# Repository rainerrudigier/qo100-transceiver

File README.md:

# QO100 SDR Transceiver Projekt für narrowband Betrieb

## Info

In diesem Github Repo sind die Infos zum OE9 QO-100 Transceiver Project aus dem Jahr 2021/22. Weiter Infos sind auch im QSP 9/22, 10/22 und 11/22 zu finden.

Die Teile des Projekts welche vom Team selbst erstellt wurden sind Open-Source. Sollten diese Teile des Projekts weiter verwendet werden erfolgt das [as-is und ohne Gewähr](/LICENSE).
Für die Fertig-Komponenten die verwendet wurden gelten die entsprechenden Lizenzen und Terms.

## Ziel des Projekts

Ziel ist der Aufbau eines kompakten und einfachen Transceivers für den narrowband (NB) SSB Betrieb über den Amateurfunksatelliten QO-100. Der Aufbau sollte verständlich sein und anderen OMs ermöglichen einfach zu einem Gerät zu kommen. Das Design sollte getestet und möglichst stabil sein, damit ein einfacher Aufbau und eine einfache Bedienung möglich ist.

## Design Kriterien

- Kompakter Aufbau - Formfaktor eines ICOM 7300 (H/B/T 90 / 240 / 238 mm)
- Zentrale Komponente für den Transceiver ist der Adalm PlutoSDR Rev D (Clock Einspeisung ohne Umbau)
- 2400MHz TX über db4um 1W pre-amp und SG-Labs AMP2400 Version 2 20W PA - Es wurde bewusst die V2 Variante gewählt, da die Version 3 Variante: (a) 40mW (16 dBm) Eingangssignal braucht, was zuviel output für den Pluto ist; und (b) es (scheinbar) Probleme mit der Stabilität gibt
- LNBP sollte kurzschlussfest sein; Schutz des Bias-T bei Kurzschluss 
- Anschluss des Systems über USB zum Laptop
- Verwendung der [SDR-Console](https://www.sdr-radio.com/download) von Simon Brown 
- Nur  narrowband (NB) Betrieb - wideband (WB) würde zu viele Änderungen brauchen (Filter, PA,...); der Aufbau wird dann zu komplex
- System sollte von Standard 13.8V DC betrieben werden können (ein Betrieb bis 24V DC wäre gut) (Anschluss Anderson PowerPole)
- Anzeige der wichtigsten Betriebsparameter über ein 4x20 LCD display (Leistung, SWR,...)
- PTT Steuerung - sowohl Betrieb über Fußschalter mit Rückmeldung an die SDR-Console und Betrieb über die SDR-Console mit Aktivierung remote PTT
- PA Abschaltung bei schlechtem SWR - Blockierung der PTT
- Keine remote Bedienelemente im Gehäuse selbst (SDR-Console unterstützt MIDI basierte remote Steuerung); wenn benötigt als abgesetztes eigenständiges Gerät

## Blockschaltbild

## Adalm Pluto

Der Analog Devices [Adalm PlutoSDR](https://wiki.analog.com/university/tools/pluto) ist die Zentrale Komponente für den SDR Transceiver - er ermöglicht das Empfang und Senden von 325Mhz - 3.8GHz; mit 200kHz - 20MHz Bandbreite. Damit wird ermöglicht dass 739-740MHz downlink QO-100 IF Signal vom LNB zu empfangen und das 2400MHz uplink Signal direkt zu erzeugen

Hardware Details können unter [Analog Wiki](https://wiki.analog.com/university/tools/pluto/hacking/hardware) gefunden werden

### Firmware

Update firmware auf letzten Stand (May 2021 -> V0.33) sollte gemacht werden. Details können auf im [Analog Wiki](https://wiki.analog.com/university/tools/nopluto/users/firmware) gefunden werden.

Der Update wird über das emulierte USB Drive des Plutos gemacht.

[Firmware Sourcecode](https://github.com/analogdevicesinc/plutosdr-fw) und [HDL Code](https://github.com/analogdevicesinc/hdl/tree/hdl_2016_r2/projects/pluto) kann auf github gefunden werden 

Eine Firmware Variante die im DATV Bereich verwendet ist bekommt man von F5OEO - dies hat auch noch ein paar extra Features wie PTT über die GPIO pins am Pluto - für den NB SSB Betrieb ist diese PTT Variante aber zu langsam - [github F5OEO](https://github.com/F5OEO/plutosdr-fw)

### Treiber

Treiber für den Adalm PlutoSDR können auch vom [Analog Wiki](https://wiki.analog.com/university/tools/pluto/drivers/windows) heruntergeladen werden

Die Treiber werden für die COM und RNDIS Schnittstellen gebraucht - da der Pluto Ethernet over USB macht.

Wenn die Treiber installiert sind kann man per Putty (oder anderem SSH client) auf den Pluto zugreifen

Zugriff auf die Konsole wird gebraucht um die verschiedenen Parameter (e.g. externe Clock) einzustellen.

Die SDR Console verwendet auch die RNDIS Ethernet Schnittstelle für die Verbindung.

## Externer Clock

### Pluto Rev D

Mit der Rev D des PlutoSDR kann dieser ohne Umbau direkt mit einem externen Clock signal versorgt werden; bei den älteren Revisionen musst durch Umbau entweder ein stabilerer (+/- 0.2 ppm) TCXO oder ein externer GPSDO Anschluss eingebaut werden (auslöten des TCXO am Pluto und Einbau einer SMA Buchse).

Das Einspeisen eines externen Clocks ist nötig um die benötigte Frequenzstabilität zu erreichen; um NB SSB Betrieb fahren zu können, da mit Sprachkanälen im kHZ bandbreiten Bereich gearbeitet wird; und ein ständiges nachjustieren der Frequenz extrem mühsam ist. 

Der primäre Fokus beim Clock des PlutoSDR ist die TX Frequenz Mischer stabilisierung - der downlink Mischer im LNB wird über modifizieren des LNB (Einbau TCXO) oder die PSK Bake stabilisiert.

Für unseren Einsatz wird die Einspeisung eines 40MHZ clocks angewendet welcher von einem Leo Bodnar GPSDO erzeugt wird; wie im Blockschaltbild dargestellt

Zum Anschluss muss ein u.FL auf SMA pigtail verwendet werden das am CLK_IN Eingang angeschlossen wird und am GPSDO - uU muss ein Dämpfungsglied zwischen GPSDO und Pluto verwendet werden damit die **max +10dBm** Eingangsleistung (an 50Ohm) nicht überschritten werden.

Die Aktivierung des CLK_IN erfolgt über einen GPIO Pin des FPGAs und wird über eine Umgebungsvariable im Linux des Plutos aktiviert

Unter https://wiki.analog.com/university/tools/pluto/devs/booting ist die entsprechende Information zu finden bzgl den Umgebungsvariablen für den clock

Umgebungsvariablen werden zB so gesetzt (siehe https://wiki.analog.com/university/tools/pluto/users/customizing) 

Die Standardwerte beim Pluto sind die Nutzung des internen clocks; und die Werkskalibierung des TXCO

Folgendes muss ausgeführt werden um den refclk auf die externe 40MHz source zu stellen

```
fw_setenv refclk_source external
fw_printenv refclk_source
#
fw_setenv ad936x_ext_refclk_override "<40000000>"
fw_printenv ad936x_ext_refclk_override
#
fw_setenv ad936x_skip_ext_refclk 1
fw_printenv ad936x_skip_ext_refclk
#
pluto_reboot reset
#
```

Werte können mit folgendem Kommando überprüft werden

```
# fw_printenv | grep refclk | grep -v setenv
```

### Umbau Rev B Pluto

*TODO infos einfuegen*

## Transceiver System Clock Erzeugung

Für den Betrieb mit QO-100 müssen die System Frequenzen stabilisiert werden. Grundsätzlich gibt es zwei Bereiche für welche ein stabiler Clock wichtig ist:

1. **PlutoSDR 40MHz Clock** - hier ist der Fokus nicht primär auf der absoluten Frequenz selbst - jedoch muss diese “langzeit” stabil sein i.e. kein driften und möglichst kleines Phasenrauschen. Ein driften und/oder wobbeln der Frequenz führt dazu das die Ausgangs Frequenz schwankt - da die 40MHz System Frequenz auf 2400MHz hoch gemischt werden; der standardmäßig verbaute TCXO ist im Bereich von  ±25ppm - was nicht ausreicht um einen stabilen Betrieb zu machen.
2. **LNB downconvert auf IF** - im LNB wird durch einen Mischer das 9.75GHz Eingangssignal auf 740MHz (für QO-100) herunter gemischt - dafür wird je nach LNB ein 25MHz oder 27MHz Quarz verwendet (DRO Varianten können nicht verwendet werden) welche die 9.75GHz Mischer Frequenz erzeugt - im regulären TV SAT betrieb wird der Träger vom Satelliten Software technisch gelocked - dadurch ist ein Frequenzdrift durch Temperatur oder andere Einflüsse nicht weiter tragisch. Diese Methode kann auch für QO-100 (PSK baken synchronisation) angewendet werden, ist jedoch nicht immer zuverlässig; es kann aber auch das LNB umgebaut werden und entsprechen per TCXO oder GPSDO mit einem stabilen CLK versorgt werden.

Für die Versorgung des Systems mit einem stabilen Clock wurde die GPSDO Variante gewählt. Der PlutoSDR und das LNB werden mit einem GPSDO von Leo Bodnar versorgt.

## GPSDO Clock Leo Bodnar

Der [zwei Kanal GSPDO von Leo Bodnar](http://www.leobodnar.com/shop/index.php?main_page=product_info&cPath=107&products_id=234) ist ein GPS disziplinierter TCXO auf der Basis eines UBLOX GPS Modules und einer Clock PLL (Si5328C) mit TCXO.

Der UBLOX kann einen stabilen Puls mit der Frequenz von 1Hz bis 10MHz liefern. Der SI5328C kann dann durch die entsprechende Parameter die Ausgänge beschalten. Der TCXO am SI5328C wird als basis verwendet und entsprechend dem GPS puls gezogen. Dadurch entsteht eine sehr genau, stabile und low-jitter Ausgangs Frequenz.

*TODO blockschaltbild einfügen*

Der GPSDO kann mittels eine einfachen Software konfiguriert werden und entsprechende eingestellt werden das er 40MHz und 25MHz liefert. Die entsprechende Parameter müssen selbst eingegeben werden - da die SW selbst nur bestimmt Frequnz kombination Standardmäßig zulässt.

Beim startup des GPSDO liefert dieser den entsprechende Clock sofort; fix und lock des systems auf GPS und PLL dauert ca 30 Sek bei Kaltstart des GPS.

### Parameter für 40MHz / 25MHz

OE6MUE hat im [Amsat Forum](https://forum.amsat-dl.org/index.php?thread/2823-gpsdo-dual-channel-from-leo-bodnar-how-to-configure/&postID=8896#post8896) folgende Parameter beschrieben:

```
40mhz+25mhz einstellungen nochmal korrigiert da der jitter nicht gepasst hat, jetzt ok!!)
CKIN1: 1750000
N31: 15
N2_HS: 4
N2_LS: 12000
N1_HS: 7
NC1_LS: 20
NC2_LS: 32
"update" drücken, soft schließen und erneut öffnen, fertig
vy 73 de oe6mue, mike aus graz
```
Die verschiedenen Parameter erzeugen unterschiedlich F3 (PLL Vergleichs-) Frequenzen; laut dem Datenblatt sollte F3 möglichst hoch sein - damit der Jitter besser ist. (Daher verwende ich die Parameter welche DSPLLsim ermittelt hat 250kHz F3). 

Mit diesen Parameters wird am Output1 40MHz ausgegeben und am Output2 25MHz

### Firmware Upgrade Leo Bodnar GPSDO

**Achtung** .. Firmware Upgrade GPSDO setzt alle Werte Retour! AUCH DIE LEISTUNG AM AUSGANG! Nicht bei angeschlossenem Pluto und LNB upgraden

### Clock Einspeisung Pluto 40MHz

Mit einem Rev.D PlutoSDR kann der Systemclock direkt eingespeist werden (**max +10dBM an 50 Ohm**). Die Konfiguration zur Aktivierung des externen Clocks muss entsprechende gemacht werden.

Mit der Einstellung von 8mA Treiber Strom beim GPSDO ergibt 7.7 dBm an 50 Ohm; uU muss aber ein Dämpfungsglied eingesetzt werden wenn die Leistung des GPSDO zum LNB nicht ausreichend ist.

### Clock Einspeisung LNB 25MHz

Das LNB wird mit 25MHz Clock versorgt. Dafür muss das LNB entsprechend Umgebaut werden (siehe LNB )

Der Treiber Strom muss uU angepasst werden je nach Distanz zum LNB

## TX Pfad

Der TX Pfad besteht primär aus Filterung und Verstärkung; die 20W PA bietet genug Leistung um eine gute Strecke zwischen Transceiver und Antenne zu ermögliche. Das verwendete Kabel zur 2.4GHz Antenne sollte low-loss / 2.4GHz ausgelegt sein. Das Signal wird dann über eine POTY Antenne (am Feed des Spiegels) oder per Helix Antenne Richtung Satellit geschickt.

### Pluto TX RF Ausgang

Ausgang sollte nicht mit voller Leistung betrieben werden. Im oberen Leistungsbereich ist der PlutoSDR nicht linear.

[ADALM Pluto TX output power rev1.pdf (dd1us.de)](http://dd1us.de/Downloads/ADALM%20Pluto%20TX%20output%20power%20rev1.pdf)

>Einstellung an der Ausgangsleistung - sdr-console  'Drive' and 'OP Power' controls

### 2.4GHz SAW Filter

Filter für 2.4 GHz um Nebenaussendungen und/oder Mischprodukte zu filtern. Filterung erfolgt gleich nach dem PlutoSDR um mögliche Produkte nicht in weitere folge zu Verstärken und ggf auszusenden 

### 2.4GHz Vor-Verstärker - db4um 2.5W

[db4um 2.5W PA (SKY66292-11)](https://github.com/db4um/PA_13cm_2W)

### 2.4GHz Power Verstärker - SG-Labs 20W Version 2

Als Power PA wird der [SG-Labs 20W Version 2](https://www.sg-lab.com/AMP2400/amp2400.html) Verstärker verwendet. Es wurde bewusst die Version 2 gewählt; da die Version 3 in Kombination mit dem Pluto sub-optional ist durch die input Power Anforderungen der V3 PA (40mW / 16dBM); der Pluto würde dann mit max power laufen und damit uU nicht-linear

Die Ausgangsleistung kann über die Spannungsversorgung (24 - 28 V DC) geregelt werden.

Umbau bzgl VSWR Messung siehe *TODO infos einfuegen*

Achtung Jumper setting auf Position 1 .. PTT on wenn PTT input auf GND *TODO infos einfuegen*

### POTY Antenne

#### Aufbau Poty

[POTY G0MJW / PA3FYM / M0EYT](http://www.hybridpretender.nl/poty.html) -- [PDF](http://www.hybridpretender.nl/patch.pdf)

[Infos von OE7WPA bzgl Patch fuer QO100](https://oe7wpa.com/index.php/projekte/antennen/patchantennen/patchantenne-fuer-qo-100)

#### Dielektrische (RF) Linse für Poty-Feed

*TODO infos einfuegen*

## RX Pfad

### Bias-T

*TODO infos Messung/Simulation einfuegen*

### LNB Spannungsversorgung

Zum Empfang muss das LNB mit Spannungs versorgt werden. Je nach Spannung (13V oder 18V) wird die polarisation des LNB’s eingestellt. 

Für den narrowband Empfang muss das LNB vertikal polarisiert arbeiten - es muss daher mit 13V versorgt werden.

Die 13V werden aus der 5V System Versorgung mittels eines Step-Up Converters erzeugt 

### LNB

#### Funktionsweise

LNBs haben eine PLL für die Erzeugung der Oszillatorfrequenz von 9750 MHz welche für den Mischer gebraucht wird. Das ergibt zunächst eine ausreichende Stabilität für Schmalband Empfang. Die Referenz der PLL ist ein 25 MHz Quarz. Die Satelliten Ausgabe im X-Band ergibt eine ZF von 739,500 bis 740 MHz. Durch die Ungenauigkeit der 25 MHz Quarze kann die Oszillator- und damit die ZF-Frequenz bis zu einigen hundert KHz abweichen.

Für den NB (narrownband) Betrieb wird die Vertical Polarisation (13V) verwendet; für WB (wideband) Horizontale Polarisation.

Für den SDR Transceiver Aufbau haben wir uns narrowband festgelegt.

Diese Ungenauigkeit kann sich durch (a) ersetzen des Quarzes durch einen TCXO oder (b) die Einspeisung des Clocks über einen GPSDO stabilisieren. Die genaue Offset Frequenz muss dann entsprechend in der SDR-Console eingestellt werden (siehe …)

Für den Aufbau des SDR Transceivers wurde die Einspeisung des Clocks von einem Leo Bodnar GPSDO gewählt

#### Umbau LNB

*TODO infos einfuegen*

## USB Verteilung

Die verschiedenen Komponenten im Transceiver werden über USB angebunden. Aus diesem Grund wurden ein USB 2.0 HUB im Transceiver verbaut welcher die verschieden Komponenten zusammenfasst

[Zero4U UUGear](https://www.digikey.at/product-detail/de/adafruit-industries-llc/3298/1528-2083-ND/6834072)

*TODO info 0R Widerstand*

## Spannungsversorgung
Anforderungen der verschiedenen Verbraucher

```
PlutoSDR 5v / 1A
-- plutosdr ist auf 1A limitiert (schematic Seite 8 LTC4415)
USB Hub 5v / 2A
Leo Bodnar 5v / 250mA (über USB Hub)
db4um_PA 5v / 1A
PTT Steuerung & Arduino 5v / 500mA
LNBP_13V 5v / 800mA
SG-Labs PA 24-28v / 1.5A
```

### System Spannung 5V/28V

Die Variante mit den Meanwell DC/DC Wandlern wurde gewählt damit der Formfaktor des Gehäuses auf ein IC7300/IC9700 erreicht werden kann. Da die der Platzverbrauch bei der Variante mit den Meanwell Wandlern sehr gering ist.

*TODO infos einfuegen*

### LNB 13V Spannungsversorgung

Variante mit [LT1372](https://www.analog.com/en/products/lt1372.html)

*TODO infos einfuegen*

## Display und Controller für System Parameter

Das Display und der Controller basieren auf dem design von DC5ZM [Infos siehe](https://hf5l.pl/en/monitor-for-sg-lab-power-amplifier/) - das ursprüngliche Design war primär für die Messung der SG-Labs Parameter (Power DRV, REF, FWD, Spannung) - wurde aber erweitert um noch zusätzlich System Parameter des SDR Transceivers erfassen zu können. Eine Möglichkeit für das abschalten der PA PTT über einen OC Ausgang wurde auch vorgesehen für ein spätere Version, damit bei zu hohem VSWR die PA ausgeschaltet wird .Um das System erweitern zu können wurde ein I2C Port vorgesehen. Das Display wird zur Anzeige der Parameter verwendet und über einen Rotary Encoder kann der Controller gesteuert werden. Als CPU wird ein Arduino Nano verwendet.

### VSWR Messung SG-Labs 20W PA
Die SG-Labs Endstufe hat lamba/4 microstrip direct coupler am Eingang und Ausgang um die Leistung zu messen welche in die PA gehen (DRV) und was zur Antenne und von der Antenne kommt (FWD/REV).

Die verschiedenen Anschlüsse (FWD, REV, DRV) müssen über durchführungs Filter aus dem Alu Gehäuse der 20W PA herausgeführt werden.

*TODO bild einfuegen*

### GPSDO lock Anzeige
Mittels eine Photo-Transistors (OP505W) wird die LED des Leo Bodnar GPSDO an den Controller “gekoppelt” und im Display der entsprechende GPSDO status angezeigt

*TODO infos einfuegen*

## PTT Aktivierung von der SDR Console zum Transceiver

Ein USB Relais kann verwendet werden um das Transmit Signal von der [SDR Console in ein PTT Signal](https://www.sdr-radio.com/relays) umzuwandeln

Es sind einige USB Relais varianten über ebay beziehbar. Wir haben uns jedoch für den Aufbau einer eigenen Variante entschieden. 

Dies hat einen besseren Formfaktor ermöglicht und die Erweiterung für eine besser PTT Anzeige am Gehäuse.

## Gehäuse
Der Formfaktor des ICOM 7300 mit (B × H × T) 240 mm × 94 mm × 238 mm (ohne vorstehende Teile) wurde im Projekt gewählt, da dieser sehr Kompakt und portable ist.

Das Gehäuse wurde komplett aus Alumium Profil-Komponenten aufgebaut. Die verwenden [Eckprofile](https://www.heavymetal-aluminium.de/shop/aluminium/aluminiumprofile/aluminium-eloxiert-aluminiumprofile/gehaeuseprofil-1-natur-eloxiert/gehaeuseprofil-1-natur-eloxiert/) sind standard im Industrie-Gehäusebau und können auf Mass zugeschnitten werden.

## Empfangs Software (PC / Linux)

### Download und installation

Download der software von [https://www.sdr-radio.com/download](https://www.sdr-radio.com/download)

### Einrichtung

*TODO infos einfuegen*

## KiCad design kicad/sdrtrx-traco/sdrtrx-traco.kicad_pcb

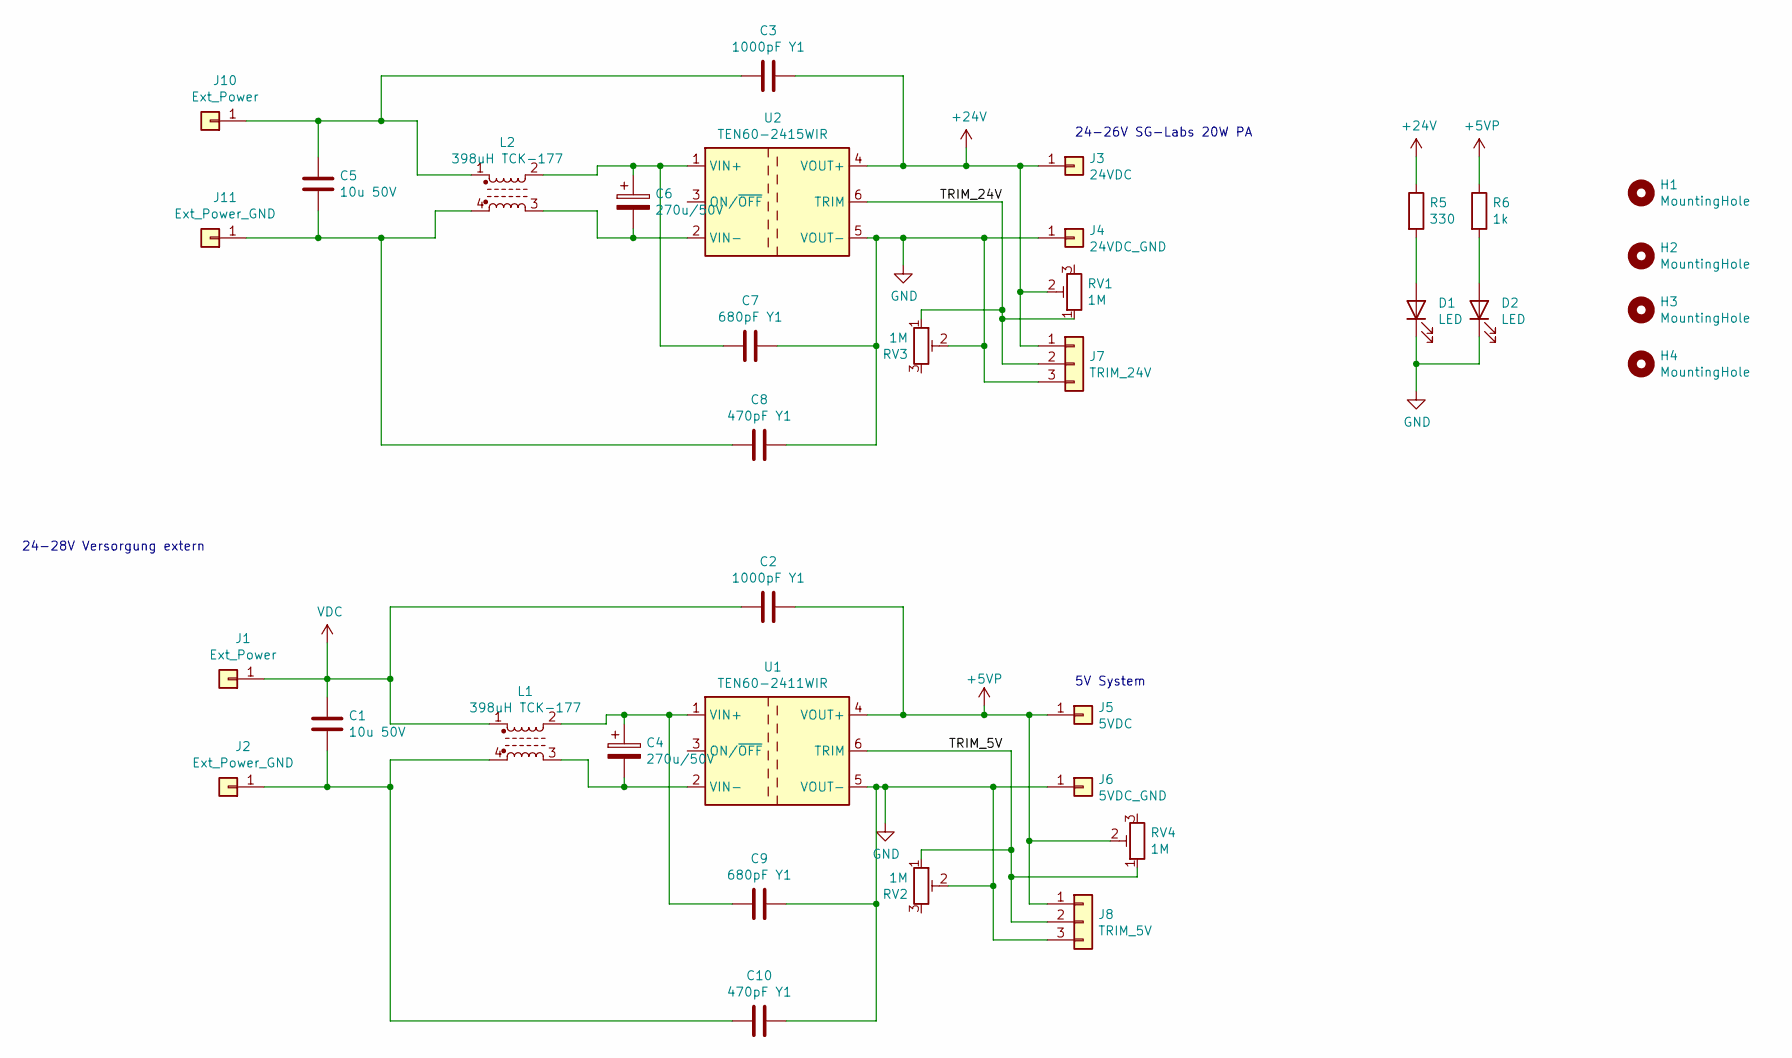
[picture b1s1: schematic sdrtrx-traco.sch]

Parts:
C1, C5: 10u 50V; C_1210_3225Metric_Pad1.42x2.65mm_HandSolder; DigiKey 399-C1210C106K5PAC7210CT-ND
C2, C3: 1000pF Y1; C_Murata_DK1; DigiKey 490-16263-1-ND
C4, C6: 270u/50V; CP_Radial_D10.0mm_P5.00mm
C7, C9: 680pF Y1; C_Murata_DK1; DigiKey 490-16263-1-ND
C8, C10: 470pF Y1; C_Murata_DK1; DigiKey 490-16263-1-ND
D1, D2: LED; LED_0805_2012Metric
H1, H2, H3, H4: MountingHole; MountingHole_3.2mm_M3_Pad
J1, J10: Ext_Power; SolderWire-1sqmm_1x01_D1.4mm_OD2.7mm
J2, J11: Ext_Power_GND; SolderWire-1sqmm_1x01_D1.4mm_OD2.7mm
J3: 24VDC; SolderWire-1sqmm_1x01_D1.4mm_OD2.7mm
J4: 24VDC_GND; SolderWire-1sqmm_1x01_D1.4mm_OD2.7mm
J5: 5VDC; SolderWire-1sqmm_1x01_D1.4mm_OD2.7mm
J6: 5VDC_GND; SolderWire-1sqmm_1x01_D1.4mm_OD2.7mm
J7: TRIM_24V; Molex_PicoBlade_53398-0371_1x03-1MP_P1.25mm_Vertical; DigiKey WM7607CT-ND
J8: TRIM_5V; Molex_PicoBlade_53398-0371_1x03-1MP_P1.25mm_Vertical; DigiKey WM7607CT-ND
L1, L2: 398uH TCK-177; Choke_Traco_TCK-177-16,0x16.0mm
R5: 330; R_0805_2012Metric
R6: 1k; R_0805_2012Metric
RV1, RV2, RV3, RV4: 1M; Potentiometer_Bourns_3269W_Vertical; DigiKey 3269W-1-105GLFCT-ND
U1: TEN60-2411WIR; Converter_DCDC_TRACO_TEN60-xxxx_THT; DigiKey 1951-TEN60-2411WIR-ND
U2: TEN60-2415WIR; Converter_DCDC_TRACO_TEN60-xxxx_THT; DigiKey 1951-TEN60-2415WIR-ND

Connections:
+5VP: C2.2, J5.1, J8.1, R6.1, RV4.2, U1.4 (VOUT+)
+24V: C3.1, J3.1, J7.1, R5.1, RV1.2, U2.4 (VOUT+)
/TRIM_5V: J8.2, RV2.1, RV4.1, U1.6 (TRIM)
/TRIM_24V: J7.2, RV1.1, RV3.1, U2.6 (TRIM)
GND: C7.1, C8.1, C9.1, C10.1, D1.1 (K), D2.1 (K), J4.1, J6.1, J7.3, J8.3, RV2.2, RV3.2, U1.5 (VOUT-), U2.5 (VOUT-)
unnamed: C1.2, C10.2, J2.1, L1.4
unnamed: C3.2, C5.1, J10.1, L2.1
unnamed: C4.1, C9.2, L1.2, U1.1 (VIN+)
unnamed: C4.2, L1.3, U1.2 (VIN-)
unnamed: C5.2, C8.2, J11.1, L2.4
unnamed: C6.1, C7.2, L2.2, U2.1 (VIN+)
unnamed: C6.2, L2.3, U2.2 (VIN-)
unnamed: D1.2 (A), R5.2
unnamed: D2.2 (A), R6.2
VDC: C1.1, C2.1, J1.1, L1.1

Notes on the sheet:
5V System
24-26V SG-Labs 20W PA
24-28V Versorgung extern

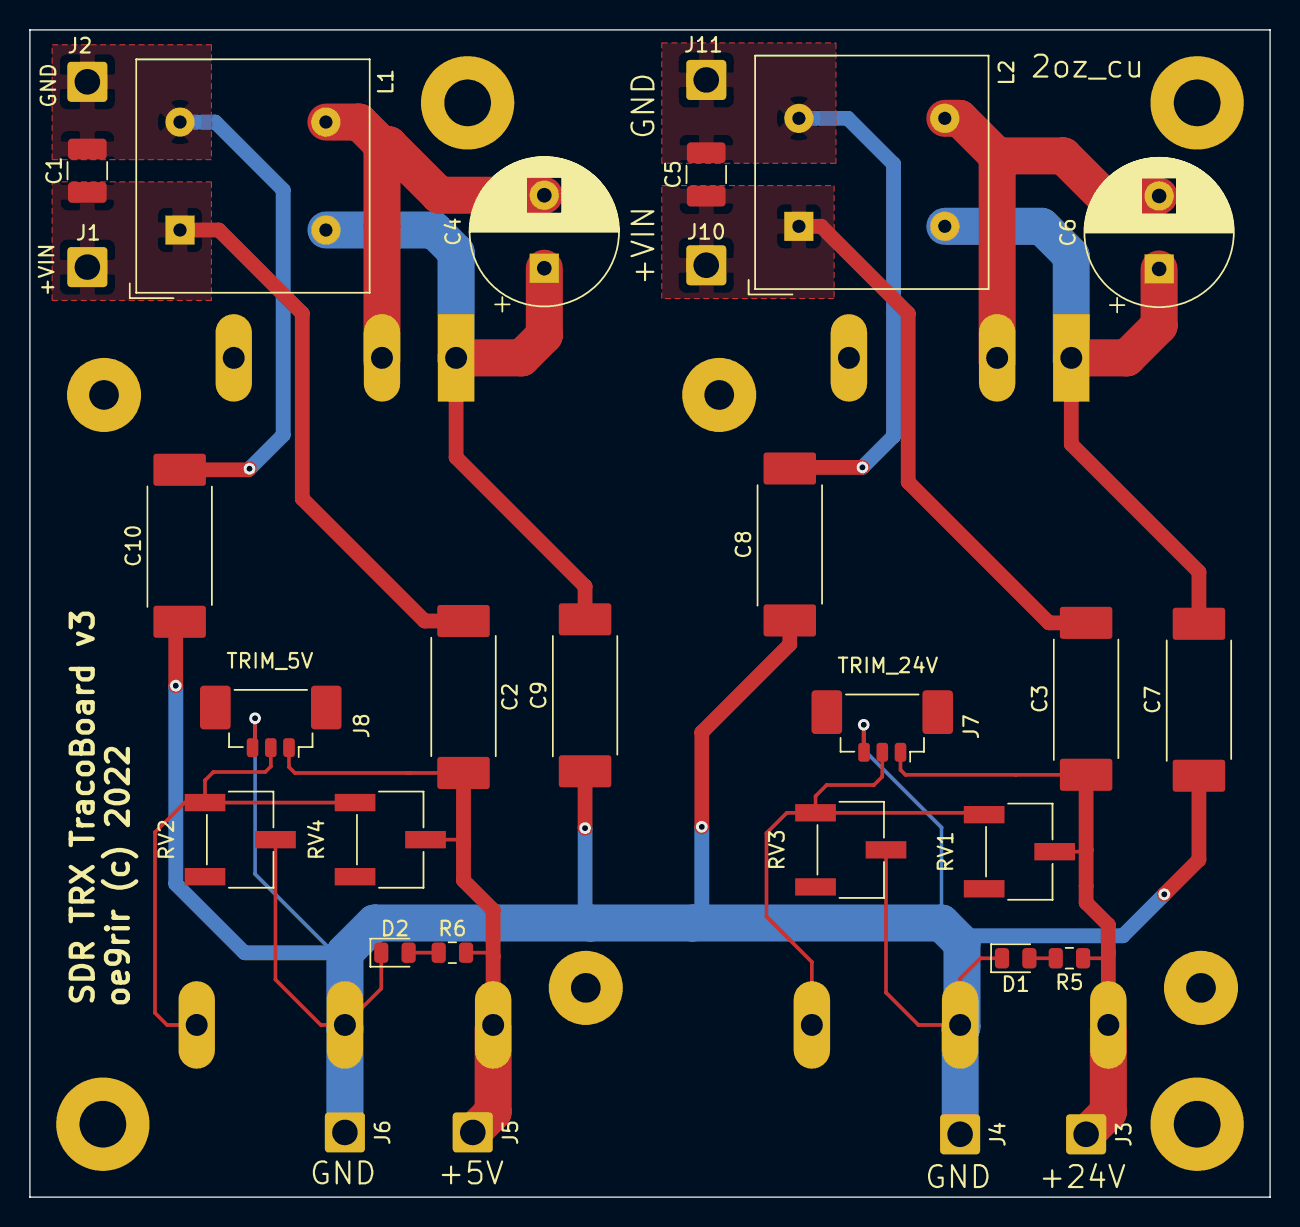
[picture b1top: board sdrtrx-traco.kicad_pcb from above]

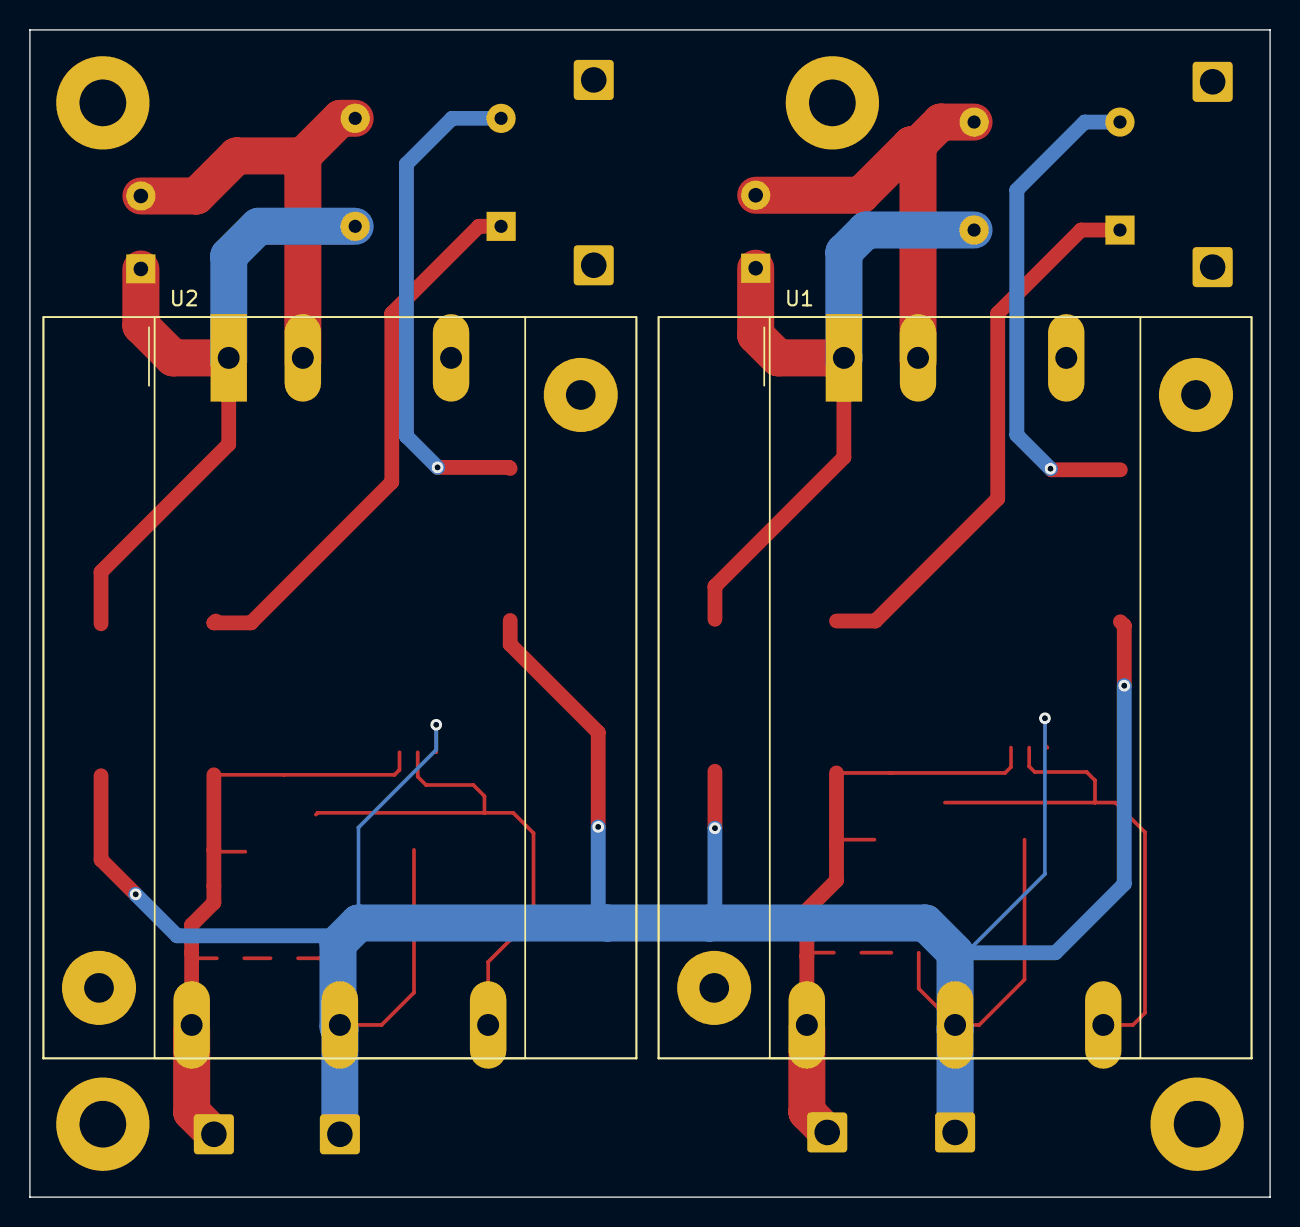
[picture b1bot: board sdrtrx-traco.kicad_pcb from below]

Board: 2 copper layers, 85.0 x 80.0 mm, 36 parts (2 on the bottom side), 15 nets.

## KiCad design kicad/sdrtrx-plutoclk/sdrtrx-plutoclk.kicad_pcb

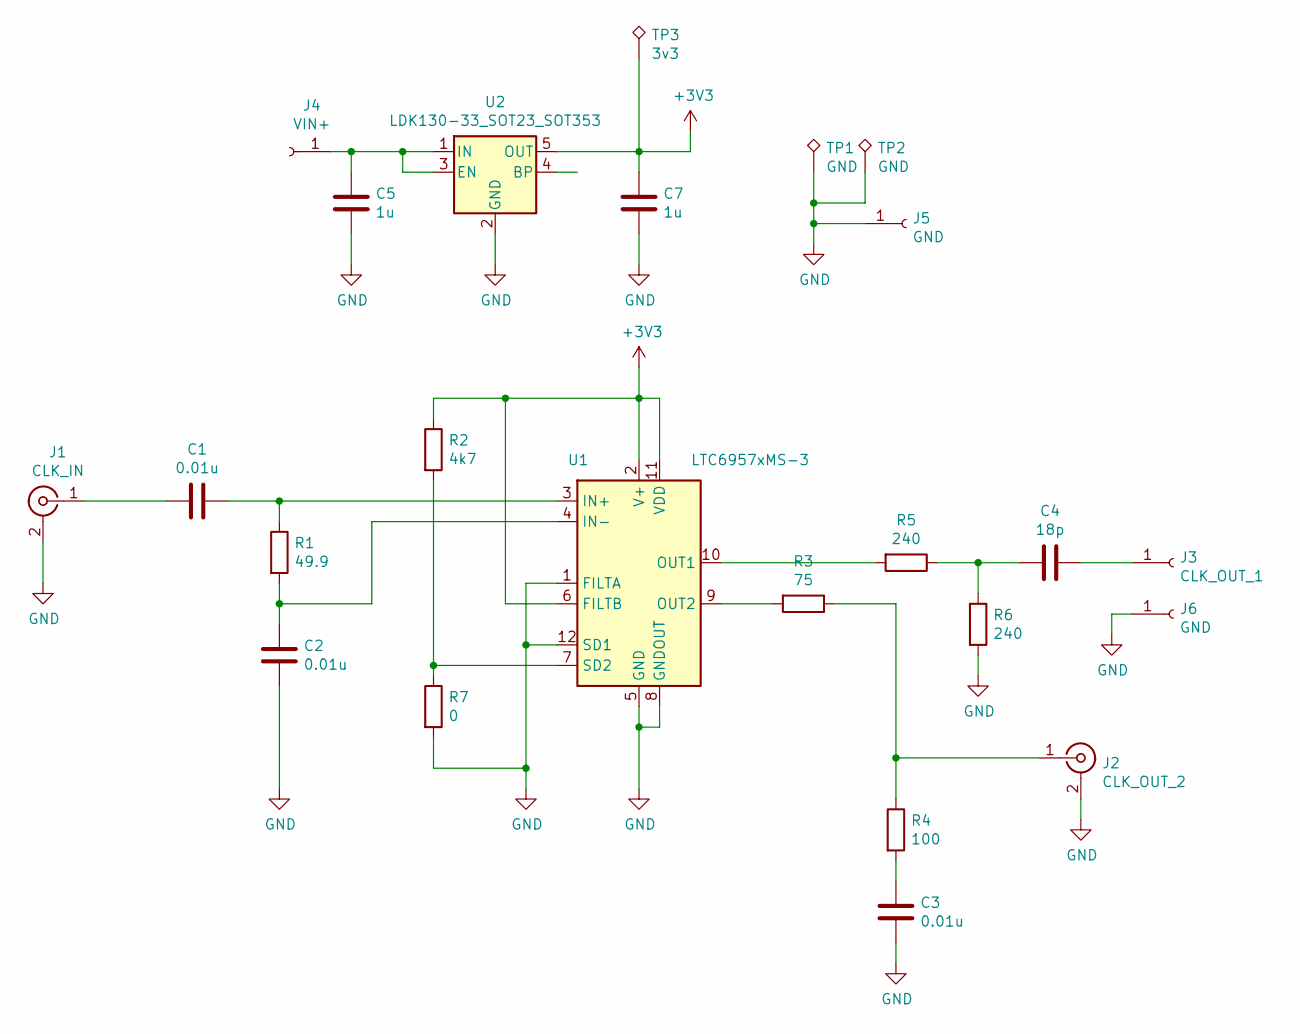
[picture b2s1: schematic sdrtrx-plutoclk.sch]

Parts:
C1, C2, C3: 0.01u; C_0603_1608Metric
C4: 18p; C_0603_1608Metric
C5, C7: 1u; C_0603_1608Metric
J1: CLK_IN; U.FL_Hirose_U.FL-R-SMT-1_Vertical
J2: CLK_OUT_2; U.FL_Hirose_U.FL-R-SMT-1_Vertical
J3: CLK_OUT_1; TestPoint_Pad_1.0x1.0mm
J4: VIN+; TestPoint_Pad_3.0x3.0mm
J5: GND; TestPoint_Pad_3.0x3.0mm
J6: GND; TestPoint_Pad_1.0x1.0mm
R1: 49.9; R_0603_1608Metric
R2: 4k7; R_0603_1608Metric
R3: 75; R_0603_1608Metric
R4: 100; R_0603_1608Metric
R5, R6: 240; R_0603_1608Metric
R7: 0; R_0603_1608Metric
TP1, TP2: GND; TestPoint_Pad_1.0x1.0mm
TP3: 3v3; TestPoint_Pad_1.0x1.0mm
U1: LTC6957xMS-3; MSOP-12_3x4mm_P0.65mm
U2: LDK130-33_SOT23_SOT353; SOT-23-5L; Mouser 511-LDK130M33RY

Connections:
+3V3: C7.1, R2.1, TP3.1, U1.2 (V+), U1.6 (FILTB), U1.11 (VDD), U2.5 (OUT)
GND: C2.2, C3.2, C5.2, C7.2, J1.2 (Ext), J2.2 (Ext), J5.1, J6.1, R6.2, R7.2, TP1.1, TP2.1, U1.1 (FILTA), U1.5 (GND), U1.8 (GNDOUT), U1.12 (SD1), U2.2 (GND)
unnamed: C1.1, R1.1, U1.3 (IN+)
unnamed: C1.2, J1.1 (In)
unnamed: C2.1, R1.2, U1.4 (IN-)
unnamed: C3.1, R4.2
unnamed: C4.1, J3.1
unnamed: C4.2, R5.1, R6.1
unnamed: C5.1, J4.1, U2.1 (IN), U2.3 (EN)
unnamed: J2.1 (In), R3.1, R4.1
unnamed: R2.2, R7.1, U1.7 (SD2)
unnamed: R3.2, U1.9 (OUT2)
unnamed: R5.2, U1.10 (OUT1)

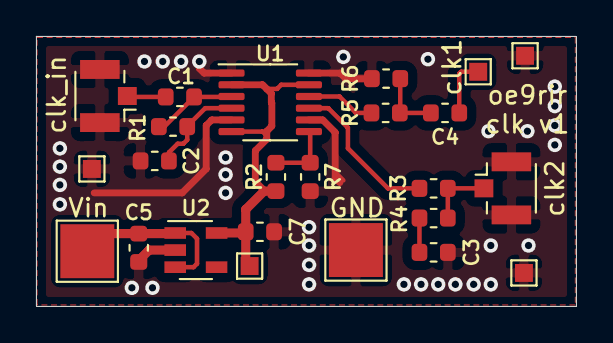
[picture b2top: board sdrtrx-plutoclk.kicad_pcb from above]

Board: 2 copper layers, 30.0 x 15.0 mm, 24 parts (0 on the bottom side), 13 nets.

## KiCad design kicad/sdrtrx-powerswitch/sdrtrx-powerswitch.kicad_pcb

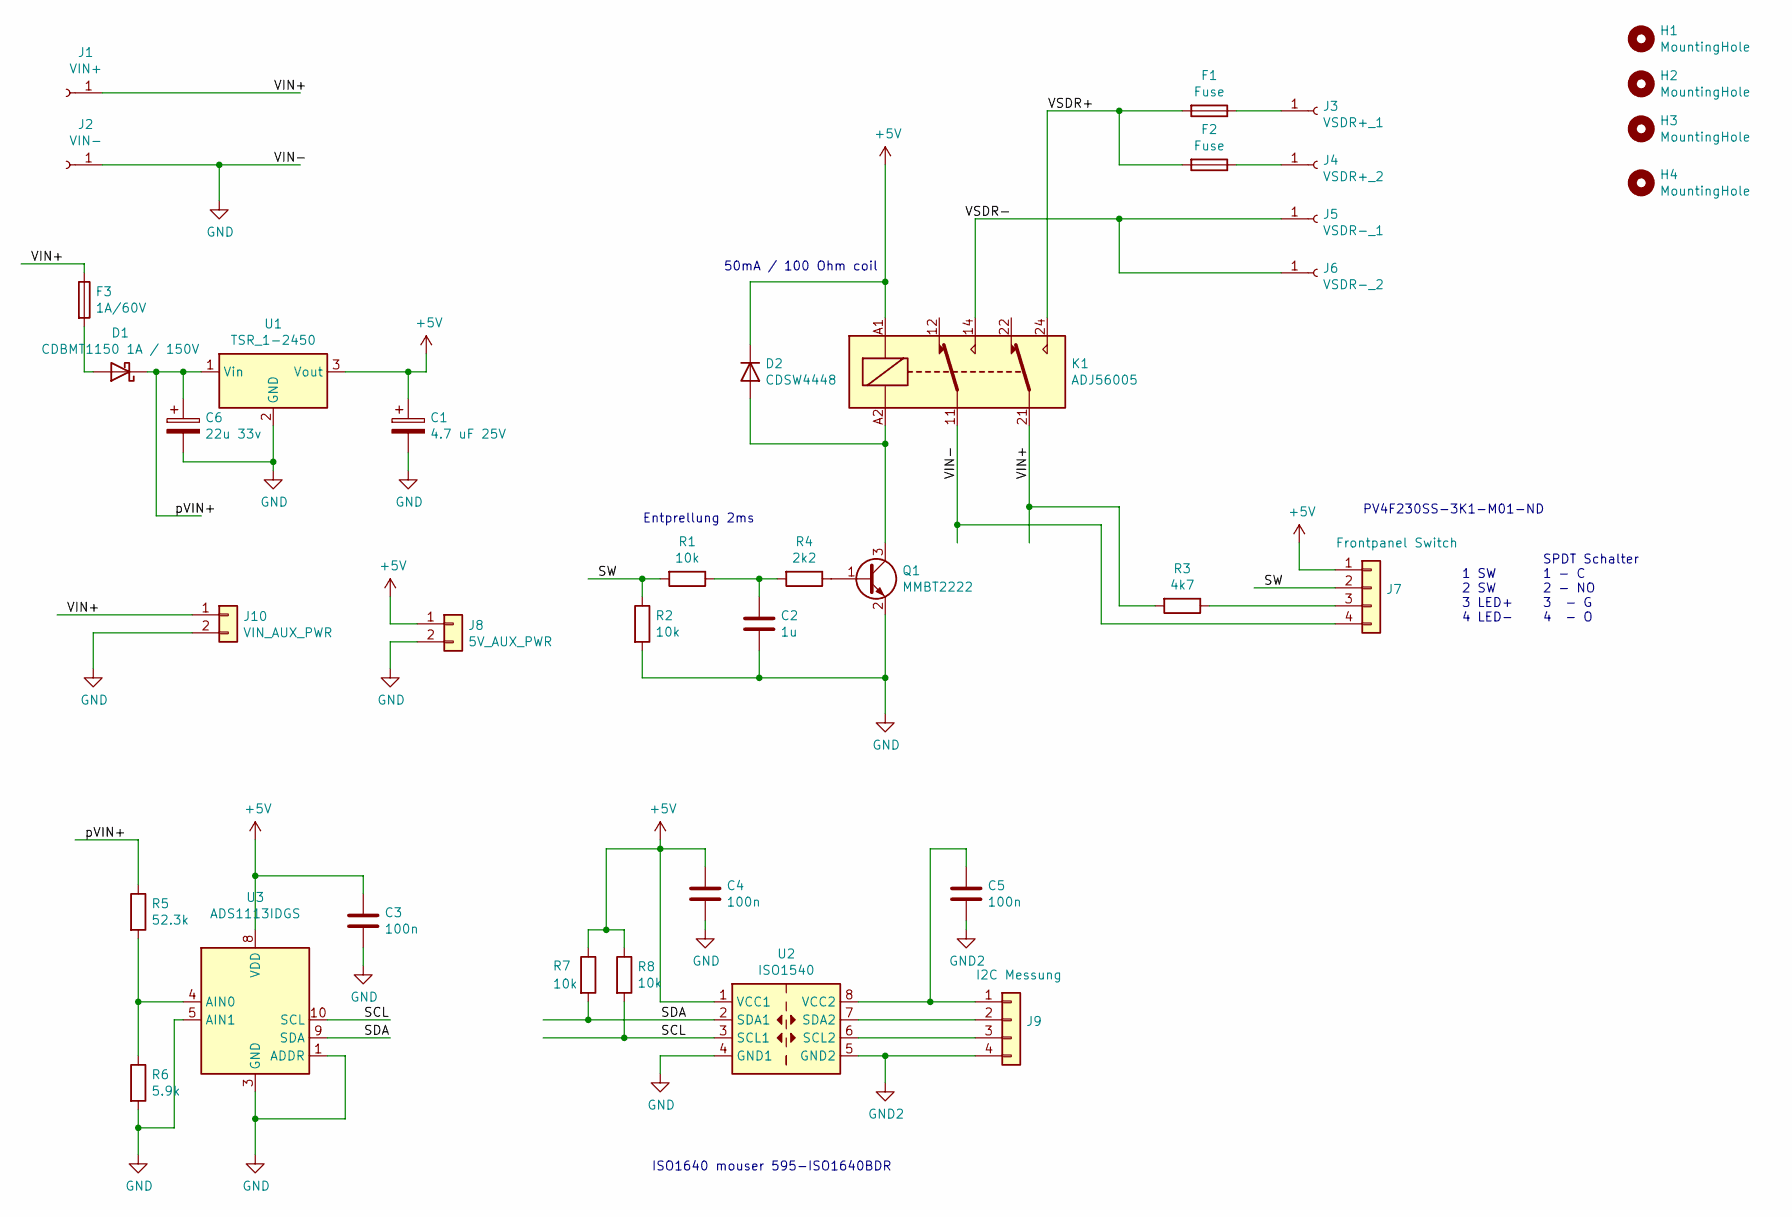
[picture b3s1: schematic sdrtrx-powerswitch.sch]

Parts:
C1: 4.7 uF 25V; CP_EIA-3528-15_AVX-H_Pad1.50x2.35mm_HandSolder; Digikey 478-11105-1-ND
C2: 1u; C_0805_2012Metric
C3, C4, C5: 100n; C_0805_2012Metric
C6: 22u 33v; CP_EIA-7343-30_AVX-N_Pad2.25x2.55mm_HandSolder
D1: CDBMT1150 1A / 150V; D_SOD-123H; Mouser 750-CDBMT1150-HF
D2: CDSW4448; D_SOD-123; Mouser 750-CDSW4448-G
F1, F2: Fuse; Fuseholder_Cylinder-5x20mm_Schurter_0031_8201_Horizontal_Op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; Mouser 693-0031.8201
F3: 1A/60V; Fuse_2920_7451Metric_Pad2.10x5.45mm_HandSolder; Digikey F8134CT-ND
H1, H2, H3, H4: MountingHole; MountingHole_3.2mm_M3_Pad
J1: VIN+; SolderWire-1sqmm_1x01_D1.4mm_OD2.7mm
J2: VIN-; SolderWire-1sqmm_1x01_D1.4mm_OD2.7mm
J3: VSDR+_1; SolderWire-1sqmm_1x01_D1.4mm_OD2.7mm
J4: VSDR+_2; SolderWire-1sqmm_1x01_D1.4mm_OD2.7mm
J5: VSDR-_1; SolderWire-1sqmm_1x01_D1.4mm_OD2.7mm
J6: VSDR-_2; SolderWire-1sqmm_1x01_D1.4mm_OD2.7mm
J7: Frontpanel Switch; Molex_PicoBlade_53398-0471_1x04-1MP_P1.25mm_Vertical
J8: 5V_AUX_PWR; JST_XH_B2B-XH-AM_1x02_P2.50mm_Vertical
J9: I2C Messung; Molex_PicoBlade_53398-0471_1x04-1MP_P1.25mm_Vertical
J10: VIN_AUX_PWR; JST_XH_B2B-XH-AM_1x02_P2.50mm_Vertical
K1: ADJ56005; Relay_DPDT_Panasonic_ADJ56005; Mouser 769-ADJ56005
Q1: MMBT2222; SOT-523; Digikey MMBT2222AT-FDICT-ND
R1, R2, R7, R8: 10k; R_0805_2012Metric
R3: 4k7; R_0805_2012Metric
R4: 2k2; R_0805_2012Metric
R5: 52.3k; R_0805_2012Metric
R6: 5.9k; R_0805_2012Metric
U1: TSR_1-2450; Converter_DCDC_TRACO_TSR-1_THT; Mouser 495-TSR-1-2450
U2: ISO1540; SOIC-8_3.9x4.9mm_P1.27mm
U3: ADS1113IDGS; TSSOP-10_3x3mm_P0.5mm

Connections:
+5V: C1.1, C3.1, C4.1, D2.1 (K), J7.1, J8.1, K1.A1, R7.1, R8.1, U1.3 (Vout), U2.1 (VCC1), U3.8 (VDD)
/SCL: R8.2, U2.3 (SCL1), U3.10 (SCL)
/SDA: R7.2, U2.2 (SDA1), U3.9 (SDA)
/SW: J7.2, R1.2, R2.1
/VIN+: F3.1, J1.1, J10.1, K1.21, R3.2
/VSDR+: F1.2, F2.2, K1.24
/VSDR-: J5.1, J6.1, K1.14
/pVIN+: C6.1, D1.1 (K), R5.1, U1.1 (Vin)
GND: C1.2, C2.2, C3.2, C4.2, C6.2, J2.1, J7.4, J8.2, J10.2, K1.11, Q1.2 (E), R2.2, R6.2, U1.2 (GND), U2.4 (GND1), U3.1 (ADDR), U3.3 (GND), U3.5 (AIN1)
GND2: C5.2, J9.4, U2.5 (GND2)
unnamed: C2.1, R1.1, R4.2
unnamed: C5.1, J9.1, U2.8 (VCC2)
unnamed: D1.2 (A), F3.2
unnamed: D2.2 (A), K1.A2, Q1.3 (C)
unnamed: F1.1, J3.1
unnamed: F2.1, J4.1
unnamed: J7.3, R3.1
unnamed: J9.2, U2.7 (SDA2)
unnamed: J9.3, U2.6 (SCL2)
unnamed: Q1.1 (B), R4.1
unnamed: R5.2, R6.1, U3.4 (AIN0)

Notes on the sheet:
PV4F230SS-3K1-M01-ND
1 SW 2 SW 3 LED+ 4 LED-
ISO1640 mouser 595-ISO1640BDR
Entprellung 2ms
50mA / 100 Ohm coil
SPDT Schalter 1 - C 2 - NO 3 - G 4 - O

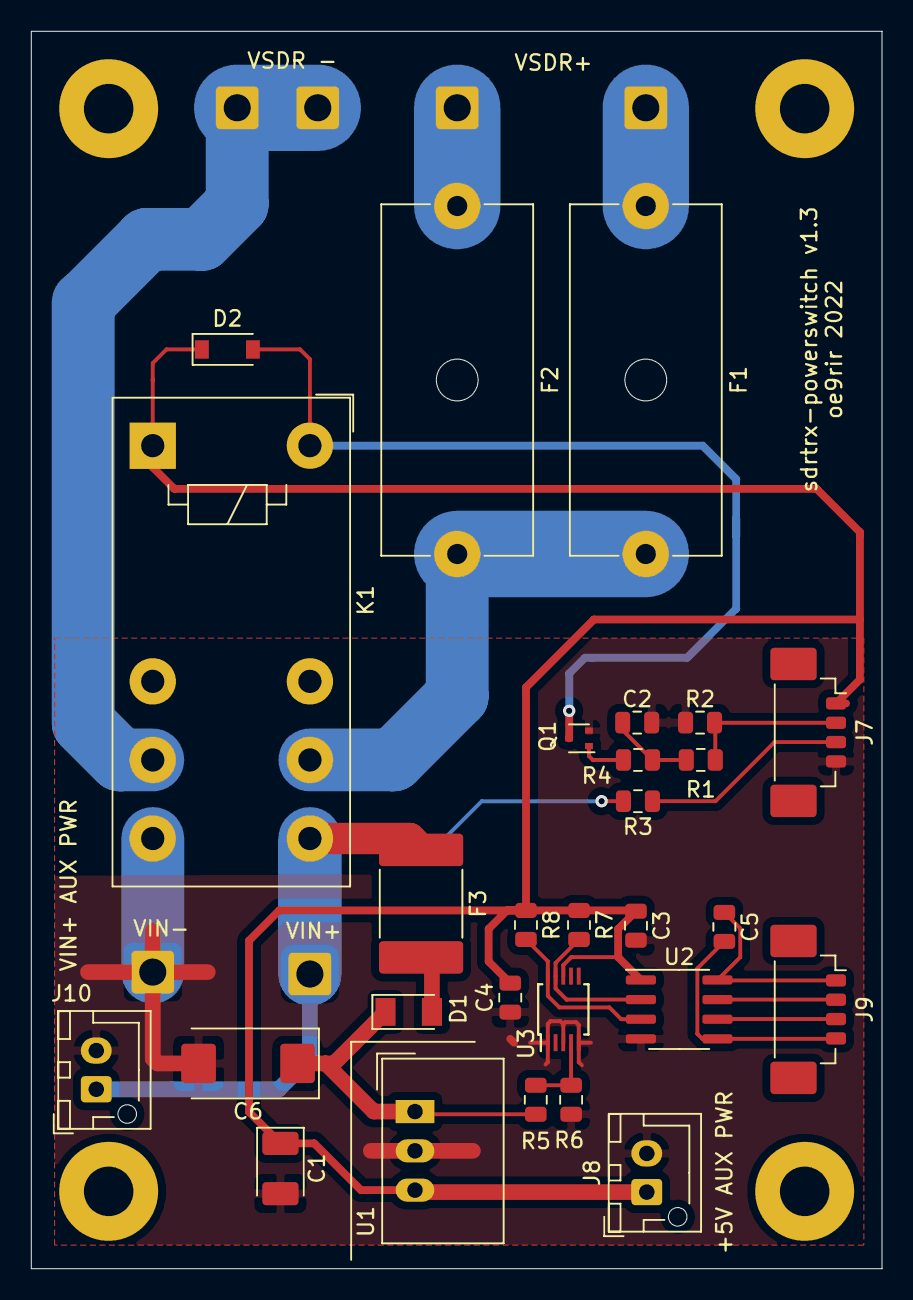
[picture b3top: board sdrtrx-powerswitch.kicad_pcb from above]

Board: 2 copper layers, 55.0 x 80.0 mm, 38 parts (0 on the bottom side), 21 nets.

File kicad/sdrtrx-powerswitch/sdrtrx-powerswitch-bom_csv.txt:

Reference, Quantity, Value, Footprint, Datasheet, Digikey, Mouser
C1 ,1,"4.7 uF 25V","Capacitor_Tantalum_SMD:CP_EIA-3528-15_AVX-H_Pad1.50x2.35mm_HandSolder","~","478-11105-1-ND",""
C2 ,1,"1u","Capacitor_SMD:C_0805_2012Metric","~"
C3 C4 C5 ,3,"100n","Capacitor_SMD:C_0805_2012Metric","~"
C6 ,1,"22u 33v","Capacitor_Tantalum_SMD:CP_EIA-7343-30_AVX-N_Pad2.25x2.55mm_HandSolder","~"
D1 ,1,"CDBMT1150 1A / 150V","Parts:D_SOD-123H","~","","750-CDBMT1150-HF"
D2 ,1,"CDSW4448","Diode_SMD:D_SOD-123","~","","750-CDSW4448-G"
F1 F2 ,2,"Fuse","Fuse:Fuseholder_Cylinder-5x20mm_Schurter_0031_8201_Horizontal_Open","~","","693-0031.8201"
F3 ,1,"1A/60V","Fuse:Fuse_2920_7451Metric_Pad2.10x5.45mm_HandSolder","~","F8134CT-ND",""
H1 H2 H3 H4 ,4,"MountingHole","MountingHole:MountingHole_3.2mm_M3_Pad","~"
J1 ,1,"VIN+","Connector_Wire:SolderWire-1sqmm_1x01_D1.4mm_OD2.7mm","~"
J10 ,1,"VIN_AUX_PWR","Connector_JST:JST_XH_B2B-XH-AM_1x02_P2.50mm_Vertical","~"
J2 ,1,"VIN-","Connector_Wire:SolderWire-1sqmm_1x01_D1.4mm_OD2.7mm","~"
J3 ,1,"VSDR+_1","Connector_Wire:SolderWire-1sqmm_1x01_D1.4mm_OD2.7mm","~"
J4 ,1,"VSDR+_2","Connector_Wire:SolderWire-1sqmm_1x01_D1.4mm_OD2.7mm","~"
J5 ,1,"VSDR-_1","Connector_Wire:SolderWire-1sqmm_1x01_D1.4mm_OD2.7mm","~"
J6 ,1,"VSDR-_2","Connector_Wire:SolderWire-1sqmm_1x01_D1.4mm_OD2.7mm","~"
J7 ,1,"Frontpanel Switch","Connector_Molex:Molex_PicoBlade_53398-0471_1x04-1MP_P1.25mm_Vertical","~"
J8 ,1,"5V_AUX_PWR","Connector_JST:JST_XH_B2B-XH-AM_1x02_P2.50mm_Vertical","~"
J9 ,1,"I2C Messung","Connector_Molex:Molex_PicoBlade_53398-0471_1x04-1MP_P1.25mm_Vertical","~"
K1 ,1,"ADJ56005","Parts:Relay_DPDT_Panasonic_ADJ56005","","","769-ADJ56005"
Q1 ,1,"MMBT2222","Package_TO_SOT_SMD:SOT-523","~","MMBT2222AT-FDICT-ND",""
R1 R2 R7 R8 ,4,"10k","Resistor_SMD:R_0805_2012Metric","~"
R3 ,1,"4k7","Resistor_SMD:R_0805_2012Metric","~"
R4 ,1,"2k2","Resistor_SMD:R_0805_2012Metric","~"
R5 ,1,"52.3k","Resistor_SMD:R_0805_2012Metric","~"
R6 ,1,"5.9k","Resistor_SMD:R_0805_2012Metric","~"
U1 ,1,"TSR_1-2450","Converter_DCDC:Converter_DCDC_TRACO_TSR-1_THT","http://www.tracopower.com/products/tsr1.pdf","","495-TSR-1-2450 "
U2 ,1,"ISO1540","Package_SO:SOIC-8_3.9x4.9mm_P1.27mm","http://www.ti.com/lit/ds/symlink/iso1541.pdf"
U3 ,1,"ADS1113IDGS","Package_SO:TSSOP-10_3x3mm_P0.5mm","http://www.ti.com/lit/ds/symlink/ads1113.pdf"

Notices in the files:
kicad/sdrtrx-arduino_v2/sdrtrx-arduino.kicad_pcb:
(c) 2022 oe9rir
kicad/sdrtrx-meanwell/sdrtrx-meanwell.kicad_pcb:
oe9rir (c) 2022
kicad/sdrtrx-power_v2.5/sdrtr-power.kicad_pcb:
oe9rir (c) 2021
